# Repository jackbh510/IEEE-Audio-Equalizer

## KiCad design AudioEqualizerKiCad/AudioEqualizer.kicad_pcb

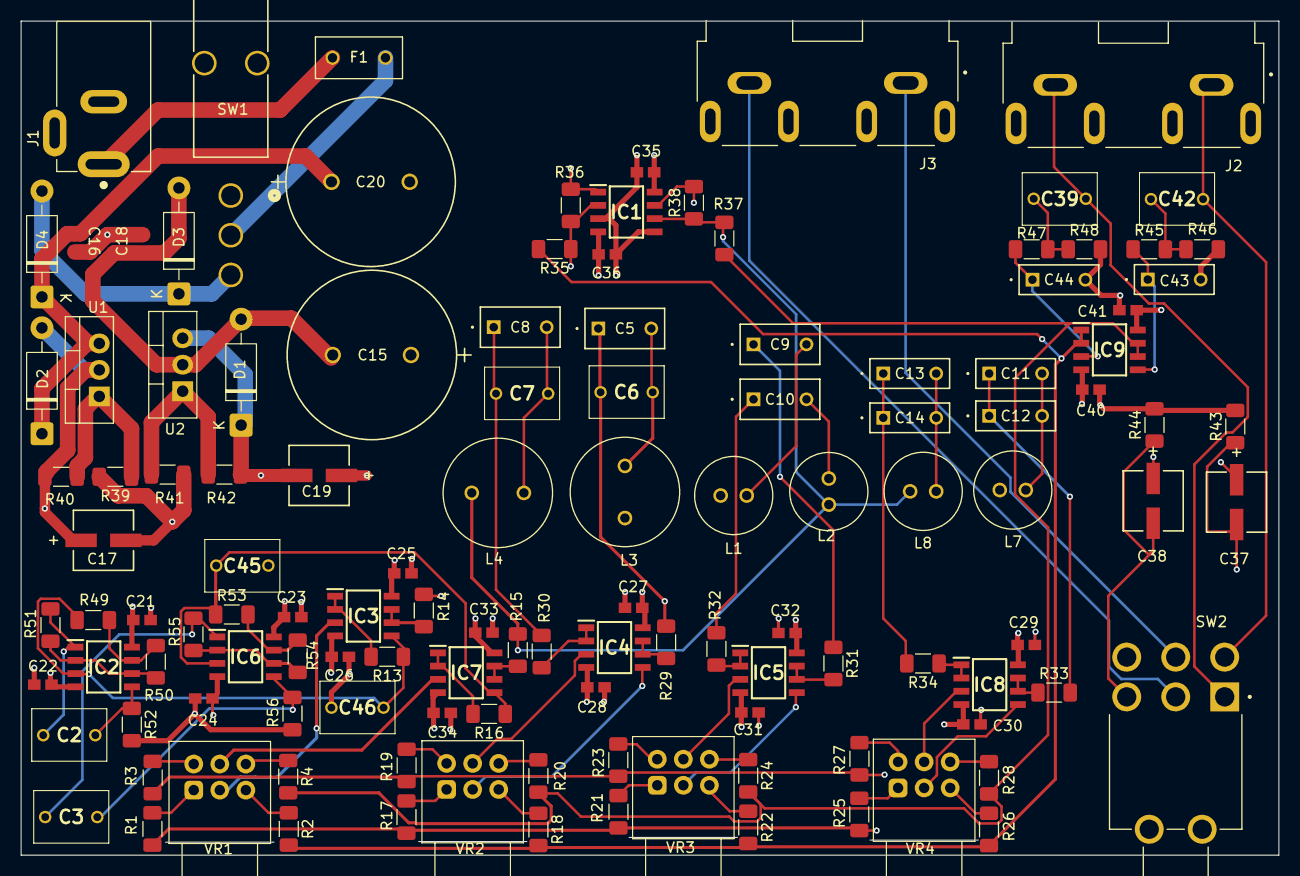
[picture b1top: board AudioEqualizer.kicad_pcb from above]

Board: 4 copper layers, 120.7 x 80.0 mm, 123 parts (0 on the bottom side), 82 nets.

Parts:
C2, C3: 1uF; R82DC4100DQ60J
C5, C8, C9, C10: .33u; CAP_R82D-7P4X3P6-5P0_KEM
C6, C7, C39, C42, C45, C46: 1u; R82DC4100DQ60J
C11, C14: 22n; CAP_R82E-7P4X2P6-5P0_KEM
C12, C13: 68n; CAP_R82E-7P4X2P6-5P0_KEM
C15, C20: 2200u; CAP_UAQ_16X25_NCH
C16, C18, C21, C22, C23, C24, C25, C26, C27, C28, C29, C30, C31, C32, C33, C34, C35, C36, C40, C41: .1u; CAPC17595_95N_KEM-M
C17, C19, C37, C38: 10u; PCAP_5x5.4-ELECT_NCA-M
C43, C44: 1n; CAP_R82E-7P4X2P6-5P0_KEM
D1, D2, D3, D4: 1N4002; D_DO-41_SOD81_P10.16mm_Horizontal
F1: 0697H0500-01; FUSRR508W60L835T400H810
IC1, IC2, IC3, IC4, IC5, IC6, IC7, IC8, IC9: NE5532DR; SOIC127P600X175-8N
J1: PJ-002A; CUI_PJ-002A
J2, J3: PJRAN2X1U01AUX; SWITCHCRAFT_PJRAN2X1U01AUX
L1, L2: 22m; IND_DRC-0608-223J-UL
L3, L4: 100m; IND_AISR-01-104J
L7, L8: 4.7m; IND_DRC-0608-472J-UL
R1, R2, R3, R4: 2.05k; R_1206_3216Metric_Pad1.30x1.75mm_HandSolder
R13, R16: 470; R_1206_3216Metric_Pad1.30x1.75mm_HandSolder
R14, R15, R33, R34: 150; R_1206_3216Metric_Pad1.30x1.75mm_HandSolder
R17, R18, R19, R20: 7.5k; R_1206_3216Metric_Pad1.30x1.75mm_HandSolder
R21, R22, R23, R24: 8.06k; R_1206_3216Metric_Pad1.30x1.75mm_HandSolder
R25, R26, R27, R28, R35, R36, R37, R38: 1.87k; R_1206_3216Metric_Pad1.30x1.75mm_HandSolder
R29, R30, R31, R32: 100; R_1206_3216Metric_Pad1.30x1.75mm_HandSolder
R39, R41: 2.74k; R_1206_3216Metric_Pad1.30x1.75mm_HandSolder
R40, R42: 249; R_1206_3216Metric_Pad1.30x1.75mm_HandSolder
R43, R44, R46, R48: 100k; R_1206_3216Metric_Pad1.30x1.75mm_HandSolder
R45, R47: 1k; R_1206_3216Metric_Pad1.30x1.75mm_HandSolder
R49, R50, R51, R52, R53, R54, R55, R56: 5k; R_1206_3216Metric_Pad1.30x1.75mm_HandSolder
SW1: 100SP1T2B4M7QE; SW3_100SP1T2B4M7QE_EWI
SW2: 100DP1T2B4M6QE; SW_100DP1T2B4M6QE
U1: LM317_TO-220; TO-220-3_Vertical
U2: LM337_TO220; TO-220-3_Vertical
VR1, VR2, VR3, VR4: 10k; Potentiometer_Alps_RK097_Dual_Horizontal

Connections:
/Gyrator/15VDC+: C17.1, C21.2, C23.1, C25.1, C27.1, C29.1, C32.1, C33.1, C35.1, C41.1, D2.2 (A), IC1.8 (VCC+), IC2.8 (VCC+), IC3.8 (VCC+), IC4.8 (VCC+), IC5.8 (VCC+), IC6.8 (VCC+), IC7.8 (VCC+), IC8.8 (VCC+), IC9.8 (VCC+), R40.1, U1.2 (VO)
/Gyrator/15VDC-: C19.2, C22.2, C24.1, C26.1, C28.1, C30.1, C31.1, C34.1, C36.1, C40.1, D1.1 (K), IC1.4 (VCC-), IC2.4 (VCC-), IC3.4 (VCC-), IC4.4 (VCC-), IC5.4 (VCC-), IC6.4 (VCC-), IC7.4 (VCC-), IC8.4 (VCC-), IC9.4 (VCC-), R42.2, U2.3 (VO)
/Gyrator/Induced_L_Left: C46.2, IC2.3 (1IN+), IC3.5 (2IN+), R13.1, R49.2
/Gyrator/Induced_L_Right: C45.2, IC6.3 (1IN+), IC7.5 (2IN+), R16.1, R53.1
/RCA(AudioINorOut)/RCA_In_L: C42.2, J2.1_A, SW2.4
/RCA(AudioINorOut)/RCA_In_R: C39.1, J2.1_B, SW2.1
/RCA(AudioINorOut)/RCA_Out_L: C37.2, R43.1, SW2.6
/RCA(AudioINorOut)/RCA_Out_R: C38.2, R44.1, SW2.3
/RLC_Cells/Sum_Left_Vin: IC9.1 (1OUT), IC9.2 (1IN-), R2.2, R18.2, R22.2, R26.2, R35.2
/RLC_Cells/Sum_Left_Vout: C38.1, IC1.1 (1OUT), R1.2, R17.2, R21.2, R25.2, R36.1
/RLC_Cells/Sum_Right_Vin: IC9.6 (2IN-), IC9.7 (2OUT), R4.2, R20.2, R24.2, R28.2, R37.1
/RLC_Cells/Sum_Right_Vout: C37.1, IC1.7 (2OUT), R3.2, R19.2, R23.2, R27.2, R38.2
/RLC_Cells/SummingL: IC1.2 (1IN-), L1.2, L3.2, L7.1, R14.2, R35.1, R36.2
/RLC_Cells/SummingR: IC1.6 (2IN-), L2.2, L4.1, L8.2, R15.2, R37.2, R38.1
GND: C15.1, C16.1, C17.2, C18.2, C19.1, C20.2, C21.1, C22.1, C23.2, C24.2, C25.2, C26.2, C27.2, C28.2, C29.2, C30.2, C31.2, C32.2, C33.2, C34.2, C35.2, C36.2, C40.2, C41.2, C43.2, C44.2, C45.1, C46.1, IC1.3 (1IN+), IC1.5 (2IN+), J1.2, J2.2_A, J2.2_B, J3.2_A, J3.2_B, R39.2, R41.1, R43.2, R44.2, R46.1, R48.2, R52.2, R56.2
unnamed: C5.1, C6.1, R29.2
unnamed: C5.2, C6.2, L3.1
unnamed: C7.1, C8.1, R30.2
unnamed: C7.2, C8.2, L4.2
unnamed: C9.1, R31.1
unnamed: C9.2, L1.1
unnamed: C10.1, R32.1
unnamed: C10.2, L2.1
unnamed: C11.1, C12.1, R33.2
unnamed: C11.2, C12.2, L7.2
unnamed: C13.1, C14.1, R34.2
unnamed: C13.2, C14.2, L8.1
unnamed: C39.2, R47.1, R48.1
unnamed: C42.1, R45.2, R46.2
unnamed: C15.2, C18.1, D1.2 (A), D3.2 (A), U2.2 (VI)
unnamed: C16.2, C20.1, D2.1 (K), D4.1 (K), U1.3 (VI)
unnamed: D3.1 (K), D4.2 (A), SW1.3
unnamed: F1.1, J1.1
unnamed: F1.2, SW1.2
unnamed: IC2.2 (1IN-), IC2.6 (2IN-), R50.1, R51.2
unnamed: C2.1, IC2.1 (1OUT), R51.1
unnamed: C2.2, IC2.5 (2IN+), R52.1
unnamed: IC2.7 (2OUT), R49.1, R50.2
unnamed: IC3.3 (1IN+), VR1.2
unnamed: IC3.1 (1OUT), IC3.2 (1IN-), R13.2
unnamed: IC3.6 (2IN-), IC3.7 (2OUT), R14.1
unnamed: IC4.3 (1IN+), VR2.5
unnamed: IC4.1 (1OUT), IC4.2 (1IN-), R30.1
unnamed: IC4.5 (2IN+), VR2.2
unnamed: IC4.6 (2IN-), IC4.7 (2OUT), R29.1
unnamed: IC5.3 (1IN+), VR3.5
unnamed: IC5.1 (1OUT), IC5.2 (1IN-), R32.2
unnamed: IC5.5 (2IN+), VR3.2
unnamed: IC5.6 (2IN-), IC5.7 (2OUT), R31.2
unnamed: IC6.2 (1IN-), IC6.6 (2IN-), R54.2, R55.1
unnamed: C3.1, IC6.1 (1OUT), R55.2
unnamed: C3.2, IC6.5 (2IN+), R56.1
unnamed: IC6.7 (2OUT), R53.2, R54.1
unnamed: IC7.3 (1IN+), VR1.5
unnamed: IC7.1 (1OUT), IC7.2 (1IN-), R16.2
unnamed: IC7.6 (2IN-), IC7.7 (2OUT), R15.1
unnamed: IC8.3 (1IN+), VR4.5
unnamed: IC8.1 (1OUT), IC8.2 (1IN-), R34.1
unnamed: IC8.5 (2IN+), VR4.2
unnamed: IC8.6 (2IN-), IC8.7 (2OUT), R33.1
unnamed: C44.1, IC9.3 (1IN+), R47.2
unnamed: C43.1, IC9.5 (2IN+), R45.1
unnamed: J3.1_A, SW2.5
unnamed: J3.1_B, SW2.2
unnamed: R1.1, VR1.1
unnamed: R2.1, VR1.3
unnamed: R3.1, VR1.4
unnamed: R4.1, VR1.6
unnamed: R17.1, VR2.1
unnamed: R18.1, VR2.3
unnamed: R19.1, VR2.4
unnamed: R20.1, VR2.6
unnamed: R21.1, VR3.1
unnamed: R22.1, VR3.3
unnamed: R23.1, VR3.4
unnamed: R24.1, VR3.6
unnamed: R25.1, VR4.1
unnamed: R26.1, VR4.3
unnamed: R27.1, VR4.4
unnamed: R28.1, VR4.6
unnamed: R39.1, R40.2, U1.1 (ADJ)
unnamed: R41.2, R42.1, U2.1 (ADJ)
